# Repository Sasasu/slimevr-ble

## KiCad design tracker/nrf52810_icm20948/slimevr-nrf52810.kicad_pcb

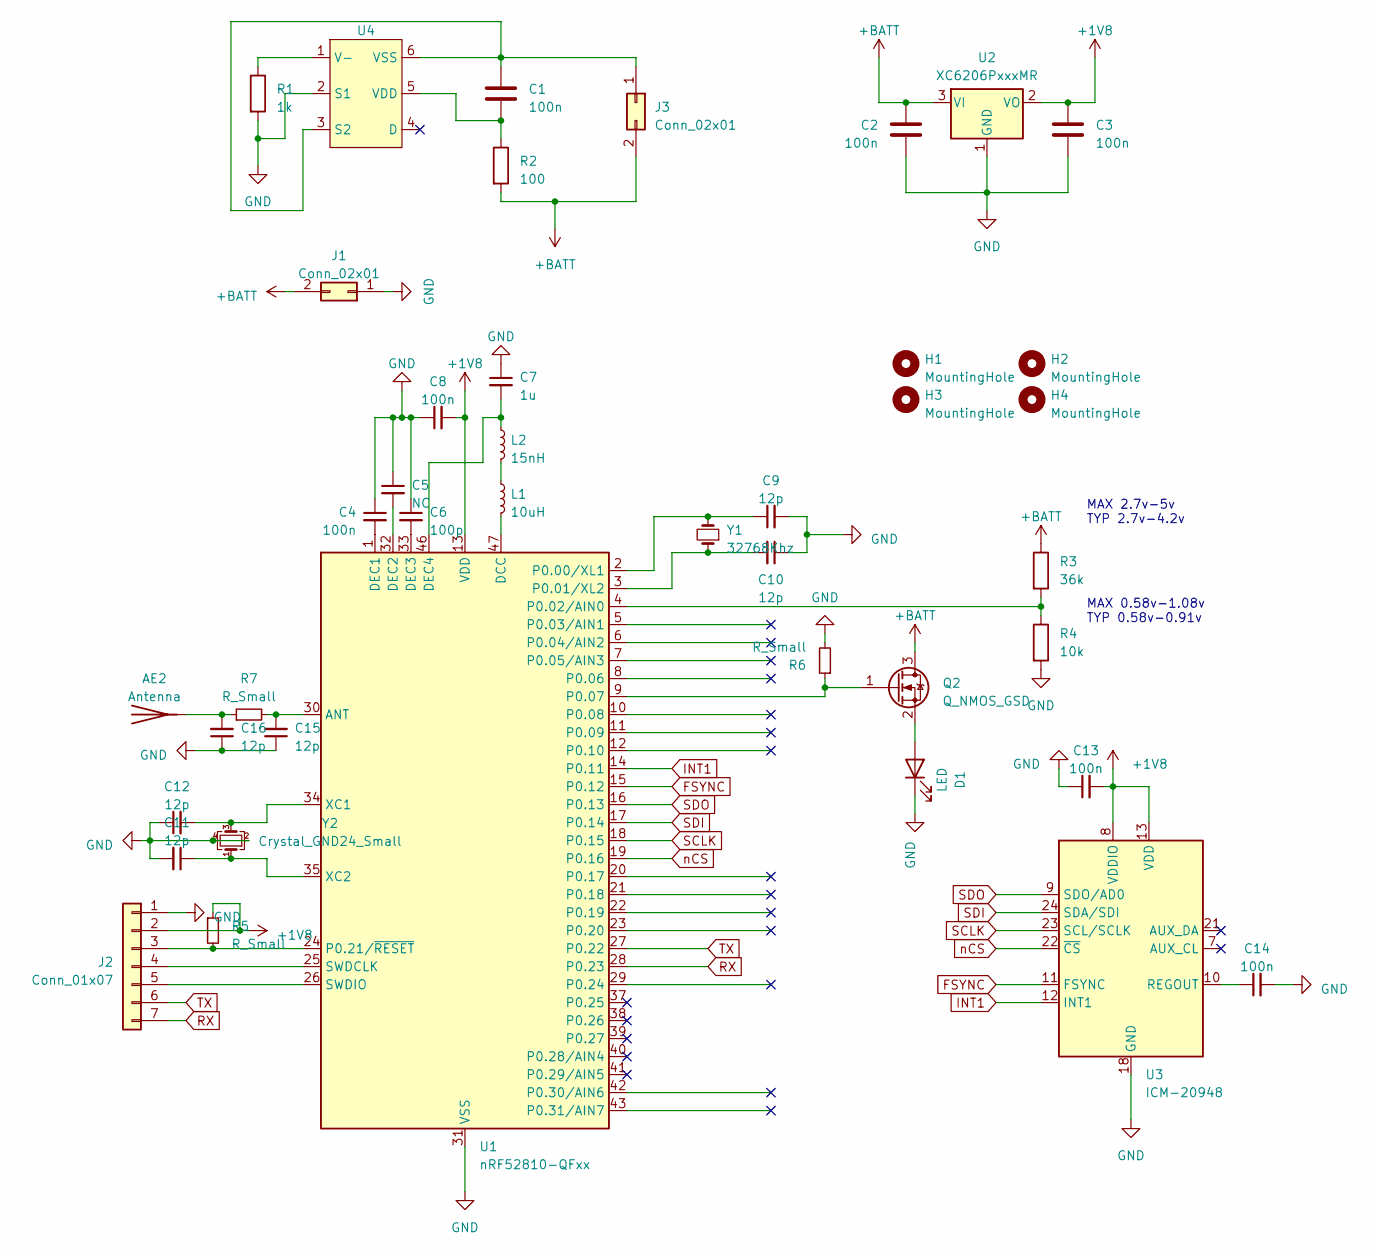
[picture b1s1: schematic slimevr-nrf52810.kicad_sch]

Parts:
AE2: Antenna; Texas_SWRA117D_2.4GHz_Right
C1, C2, C3, C4, C8, C13, C14: 100n; C_0402_1005Metric
C5: NC; C_0402_1005Metric
C6: 100p; C_0402_1005Metric
C7: 1u; C_0402_1005Metric
C9, C10, C11, C12, C15, C16: 12p; C_0402_1005Metric
D1: LED; LED_0402_1005Metric
H1, H2, H3, H4: MountingHole; MountingHole_2.2mm_M2
J1: Conn_02x01; PinHeader_1x02_P2.54mm_Vertical
J2: Conn_01x07; PinHeader_1x07_P1.00mm_Vertical
J3: Conn_02x01; PinSocket_1x02_P1.00mm_Vertical
L1: 10uH; L_1008_2520Metric
L2: 15nH; L_0402_1005Metric
Q2: Q_NMOS_GSD; SOT-23
R1: 1k; R_0402_1005Metric
R2: 100; R_0402_1005Metric
R3: 36k; R_0402_1005Metric
R4: 10k; R_0402_1005Metric
R5, R6, R7: R_Small; R_0402_1005Metric
U1: nRF52810-QFxx; QFN-48-1EP_6x6mm_P0.4mm_EP4.6x4.6mm
U2: XC6206PxxxMR; SOT-23-3
U3: ICM-20948; InvenSense_QFN-24_3x3mm_P0.4mm
U4: SOT-23-6
Y1: 32768Khz; Crystal_SMD_3215-2Pin_3.2x1.5mm
Y2: Crystal_GND24_Small; Crystal_SMD_3225-4Pin_3.2x2.5mm

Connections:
+1V8: C3.1, C8.2, C13.2, J2.2, R5.1, U1.13 (VDD), U1.36 (VDD), U1.48 (VDD), U2.2 (VO), U3.8 (VDDIO), U3.13 (VDD)
+BATT: C2.1, J1.2, J3.2, Q2.3 (D), R2.2, R3.1, U2.3 (VI)
FSYNC: U1.15 (P0.12), U3.11 (FSYNC)
GND: C2.2, C3.2, C4.1, C5.1, C6.1, C7.1, C8.1, C9.2, C10.1, C11.2, C12.1, C13.1, C14.2, C15.1, C16.1, D1.1 (K), J1.1, J2.1, R1.2, R4.2, R6.2, U1.31 (VSS), U1.45 (VSS), U1.49 (VSS), U2.1 (GND), U3.18 (GND), U3.20 (GND), U4.2 (S1), Y2.2, Y2.4
INT1: U1.14 (P0.11), U3.12 (INT1)
unnamed: AE2.1 (A), C16.2, R7.1
unnamed: D1.2 (A), Q2.2 (S)
unnamed: J2.3, R5.2, U1.24 (P0.21/~RESET)
unnamed: J2.4, U1.25 (SWDCLK)
unnamed: J2.5, U1.26 (SWDIO)
unnamed: C1.1, J3.1, U4.3 (S2), U4.6 (VSS)
unnamed: L1.1, L2.2
unnamed: Q2.1 (G), R6.1, U1.9 (P0.07)
unnamed: C15.2, R7.2, U1.30 (ANT)
unnamed: L1.2, U1.47 (DCC)
unnamed: C4.2, U1.1 (DEC1)
unnamed: C5.2, U1.32 (DEC2)
unnamed: C6.2, U1.33 (DEC3)
unnamed: C7.2, L2.1, U1.46 (DEC4)
unnamed: C9.1, U1.2 (P0.00/XL1), Y1.2
unnamed: C10.2, U1.3 (P0.01/XL2), Y1.1
unnamed: R3.2, R4.1, U1.4 (P0.02/AIN0)
unnamed: C12.2, U1.34 (XC1), Y2.3
unnamed: C11.1, U1.35 (XC2), Y2.1
unnamed: C14.1, U3.10 (REGOUT)
unnamed: R1.1, U4.1 (V-)
unnamed: C1.2, R2.1, U4.5 (VDD)
RX: J2.7, U1.28 (P0.23)
SCLK: U1.18 (P0.15), U3.23 (SCL/SCLK)
SDI: U1.17 (P0.14), U3.24 (SDA/SDI)
SDO: U1.16 (P0.13), U3.9 (SDO/AD0)
TX: J2.6, U1.27 (P0.22)
nCS: U1.19 (P0.16), U3.22 (~CS)

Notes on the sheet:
MAX 0.58v-1.08v TYP 0.58v-0.91v
MAX 2.7v-5v TYP 2.7v-4.2v

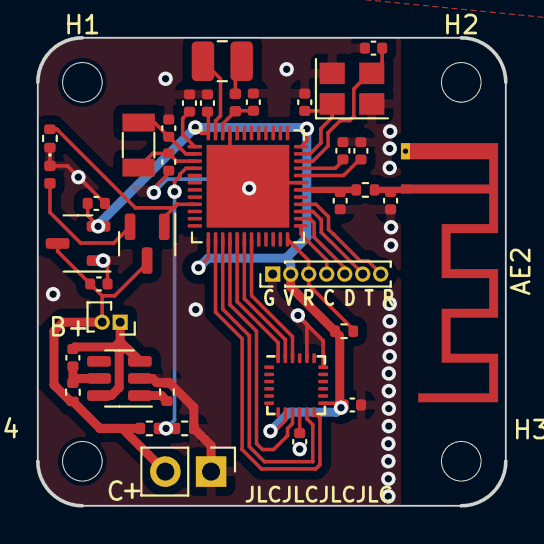
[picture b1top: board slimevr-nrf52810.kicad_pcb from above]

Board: 4 copper layers, 26.0 x 26.0 mm, 41 parts (0 on the bottom side), 33 nets.

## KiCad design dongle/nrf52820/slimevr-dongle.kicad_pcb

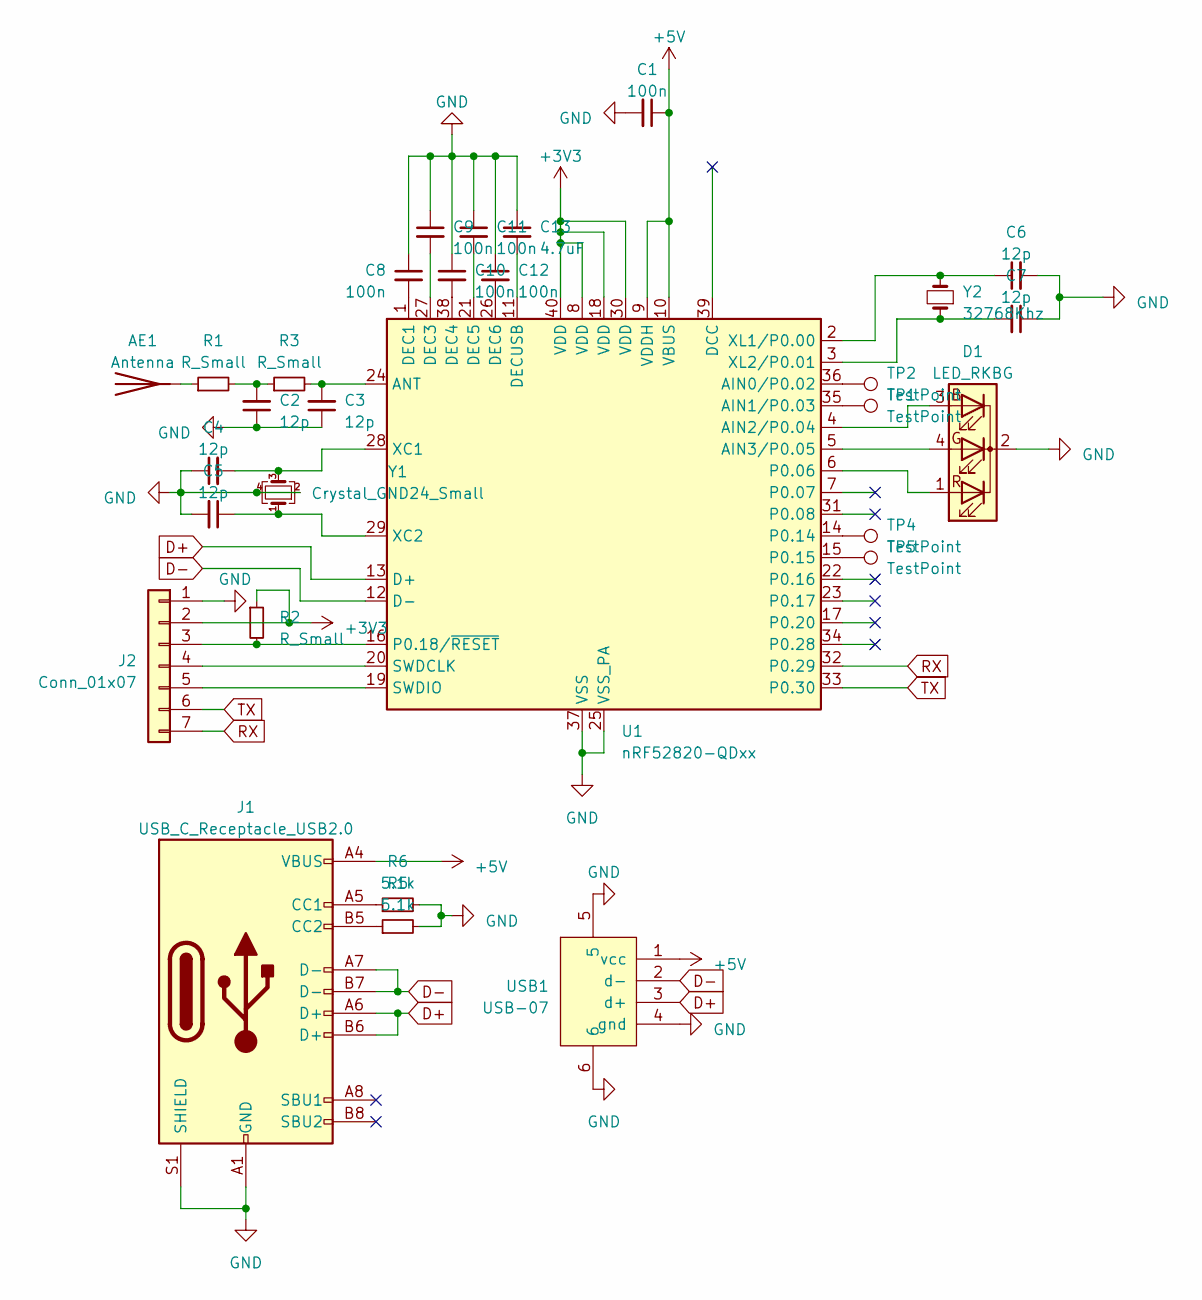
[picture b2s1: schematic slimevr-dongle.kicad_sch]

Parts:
AE1: Antenna; Texas_SWRA117D_2.4GHz_Left
C1, C8, C9, C10, C11, C12: 100n; C_0402_1005Metric
C2, C3, C4, C5, C6, C7: 12p; C_0402_1005Metric
C13: 4.7uF; C_0402_1005Metric
D1: LED_RKBG; LED_LiteOn_LTST-C19HE1WT
J1: USB_C_Receptacle_USB2.0; USB_C_Receptacle_G-Switch_GT-USB-7010ASV
J2: Conn_01x07; PinHeader_1x07_P2.54mm_Vertical
R1, R2, R3: R_Small; R_0402_1005Metric
R5, R6: 5.1k; R_0402_1005Metric
TP1, TP2, TP4, TP5: TestPoint; TestPoint_Pad_D1.0mm
U1: nRF52820-QDxx; QFN-40-1EP_5x5mm_P0.4mm_EP3.6x3.6mm
USB1: USB-07; USB-A-SMD_USB-07
Y1: Crystal_GND24_Small; Crystal_SMD_3225-4Pin_3.2x2.5mm
Y2: 32768Khz; Crystal_SMD_3215-2Pin_3.2x1.5mm

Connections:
+3V3: J2.2, R2.1, U1.8 (VDD), U1.18 (VDD), U1.30 (VDD), U1.40 (VDD)
+5V: C1.1, J1.A4 (VBUS), J1.A9 (VBUS), J1.B4 (VBUS), J1.B9 (VBUS), U1.9 (VDDH), U1.10 (VBUS), USB1.1 (vcc)
D+: J1.A6 (D+), J1.B6 (D+), U1.13 (D+), USB1.3 (d+)
D-: J1.A7 (D-), J1.B7 (D-), U1.12 (D-), USB1.2 (d-)
GND: C1.2, C2.1, C3.1, C4.1, C5.2, C6.2, C7.1, C8.1, C9.1, C10.1, C11.1, C12.1, C13.1, D1.2 (K), J1.A1 (GND), J1.A12 (GND), J1.B1 (GND), J1.B12 (GND), J1.S1 (SHIELD), J2.1, R5.2, R6.2, U1.25 (VSS_PA), U1.37 (VSS), U1.41 (VSS), USB1.4 (gnd), USB1.5, USB1.6, Y1.2, Y1.4
unnamed: AE1.1 (A), R1.1
unnamed: C2.2, R1.2, R3.1
unnamed: D1.3 (BA), U1.4 (AIN2/P0.04)
unnamed: D1.4 (GA), U1.5 (AIN3/P0.05)
unnamed: D1.1 (RA), U1.6 (P0.06)
unnamed: J1.A5 (CC1), R6.1
unnamed: J1.B5 (CC2), R5.1
unnamed: J2.3, R2.2, U1.16 (P0.18/~RESET)
unnamed: J2.4, U1.20 (SWDCLK)
unnamed: J2.5, U1.19 (SWDIO)
unnamed: TP2.1, U1.36 (AIN0/P0.02)
unnamed: TP1.1, U1.35 (AIN1/P0.03)
unnamed: C3.2, R3.2, U1.24 (ANT)
unnamed: C8.2, U1.1 (DEC1)
unnamed: C9.2, U1.27 (DEC3)
unnamed: C10.2, U1.38 (DEC4)
unnamed: C11.2, U1.21 (DEC5)
unnamed: C12.2, U1.26 (DEC6)
unnamed: C13.2, U1.11 (DECUSB)
unnamed: TP4.1, U1.14 (P0.14)
unnamed: TP5.1, U1.15 (P0.15)
unnamed: C4.2, U1.28 (XC1), Y1.3
unnamed: C5.1, U1.29 (XC2), Y1.1
unnamed: C6.1, U1.2 (XL1/P0.00), Y2.2
unnamed: C7.2, U1.3 (XL2/P0.01), Y2.1
RX: J2.7, U1.32 (P0.29)
TX: J2.6, U1.33 (P0.30)

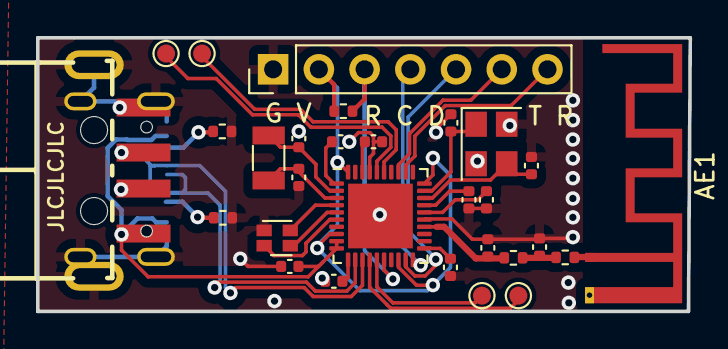
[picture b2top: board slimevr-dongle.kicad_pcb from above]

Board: 4 copper layers, 36.2 x 15.2 mm, 30 parts (1 on the bottom side), 32 nets.

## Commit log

2023-05-21 init
2023-05-28 zypher hello world
2023-06-15 wip spi test
2023-06-24 driver mode
2023-06-25 clean up
2023-06-25 triger
2023-06-25 ble driver
2023-06-26 battery
2023-06-26 connect
2023-07-09 add dmp
